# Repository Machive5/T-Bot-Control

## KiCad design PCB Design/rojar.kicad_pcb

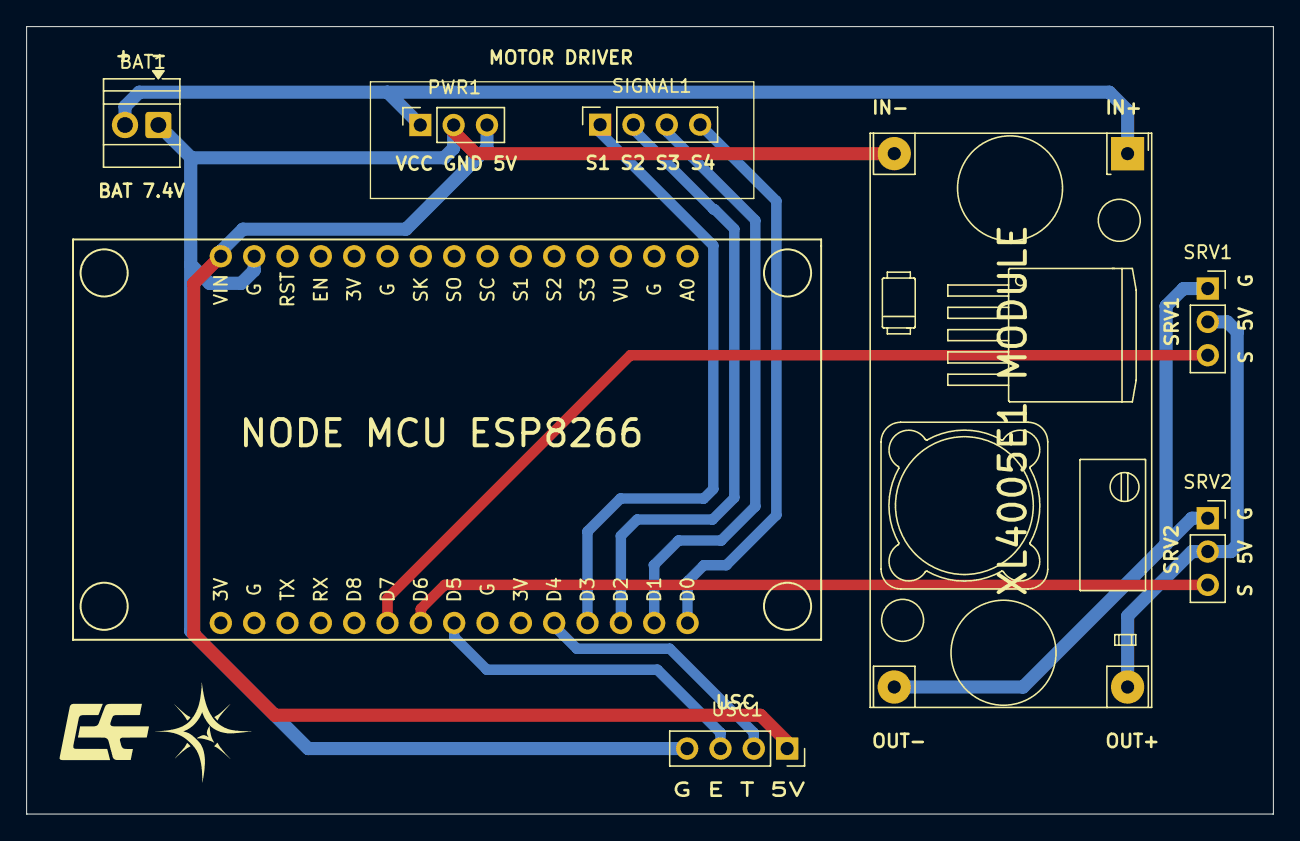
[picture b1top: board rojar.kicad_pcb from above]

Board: 2 copper layers, 95.0 x 60.0 mm, 8 parts (0 on the bottom side), 13 nets.

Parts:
BAT1: Screw_Terminal_01x02; TerminalBlock_Xinya_XY308-2.54-2P_1x02_P2.54mm_Horizontal
PWR1: Conn_01x03_Socket; PinSocket_1x03_P2.54mm_Vertical
SIGNAL1: Conn_01x04_Socket; PinSocket_1x04_P2.54mm_Vertical
SRV1, SRV2: Conn_01x03_Pin; PinSocket_1x03_P2.54mm_Vertical
U1: NodeMCU1.0(ESP-12E); NodeMCU-LoLinV3
U2: YAAJ_DCDC_StepDown_LM2596
USC1: Conn_01x04_Socket; PinSocket_1x04_P2.54mm_Vertical

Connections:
+5V: PWR1.3, U1.15 (VIN), USC1.1
/Bat: BAT1.2, PWR1.1, U2.1 (Vin)
GND: BAT1.1, PWR1.2, U1.14 (GND), U2.2 (GND), USC1.4
unnamed: SIGNAL1.1, U1.27 (D3(GPIO0))
unnamed: SIGNAL1.2, U1.28 (D2(GPIO4))
unnamed: SIGNAL1.3, U1.29 (D1(GPIO5))
unnamed: SIGNAL1.4, U1.30 (D0(GPIO16))
unnamed: SRV1.1, SRV2.1, U2.3 (GND)
unnamed: SRV1.2, SRV2.2, U2.4 (Vout)
unnamed: SRV1.3, U1.21 (D7(GPIO13))
unnamed: SRV2.3, U1.22 (D6(GPIO12))
unnamed: U1.26 (D4(GPIO2)), USC1.2
unnamed: U1.23 (D5(GPIO14)), USC1.3

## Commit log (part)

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2025-12-29 Initial commit
    Generated by react-native@0.83.1
2025-12-29 creating home screen
2026-01-03 creating network and udp communication and releasing the aplication
2026-01-04 fixing some bug
